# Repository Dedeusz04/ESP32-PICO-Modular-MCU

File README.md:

# ESP32-PICO Modular MCU

A modular hardware design based on the ESP32-PICO microcontroller, split into separate, specialized boards for the processor, power supply, and clock management to ensure high flexibility and easier troubleshooting in embedded development.

## Key Features
- **Modular Architecture**: Core system functionality is divided into distinct, easily interchangeable boards.
- **Processor Module** (`modul_procesora`): Houses the ESP32-PICO core, providing native Wi-Fi/Bluetooth capabilities and GPIO breakouts.
- **Power Supply Module** (`modul_zasilania`): Dedicated hardware for voltage regulation and stable power distribution to all components.
- **Clock Module** (`modul_zegara`): Handles precise clock generation and timing logic.
- **Custom Component Library**: Includes a comprehensive custom Autodesk EAGLE library (`proj_biblioteka.lbr`) with all necessary footprints and symbols used.

For a detailed description of the design, schematic choices, and PCB layouts, refer to the final project report included in this repository: [raport_koncowy_tem1 2 (1).pdf](raport_koncowy_tem1%202%20%281%29.pdf).

## Modules Overview
| Module | Schematic File | Board File | Description |
|---|---|---|---|
| **Processor Module** | `modul_procesora.sch` | `modul_procesora.brd` | Core ESP32-PICO system |
| **Power Supply** | `modul_zasilania.sch` | `modul_zasilania.brd` | Voltage regulation and power management |
| **Clock Module** | `modul_zegara.sch` | `modul_zegara.brd` | Precise timers and RTC |

## Usage
The hardware designs are provided as Autodesk EAGLE files.
1. Clone or download this repository.
2. Open Autodesk EAGLE and ensure `proj_biblioteka.lbr` is added to your active libraries.
3. Open the `.sch` and `.brd` files to view, modify, or manufacture the schematics and PCB designs.

## Contributors
- **Bartosz Kępa**
- **Jan Jamro**
- **Aleksandra Kuś**

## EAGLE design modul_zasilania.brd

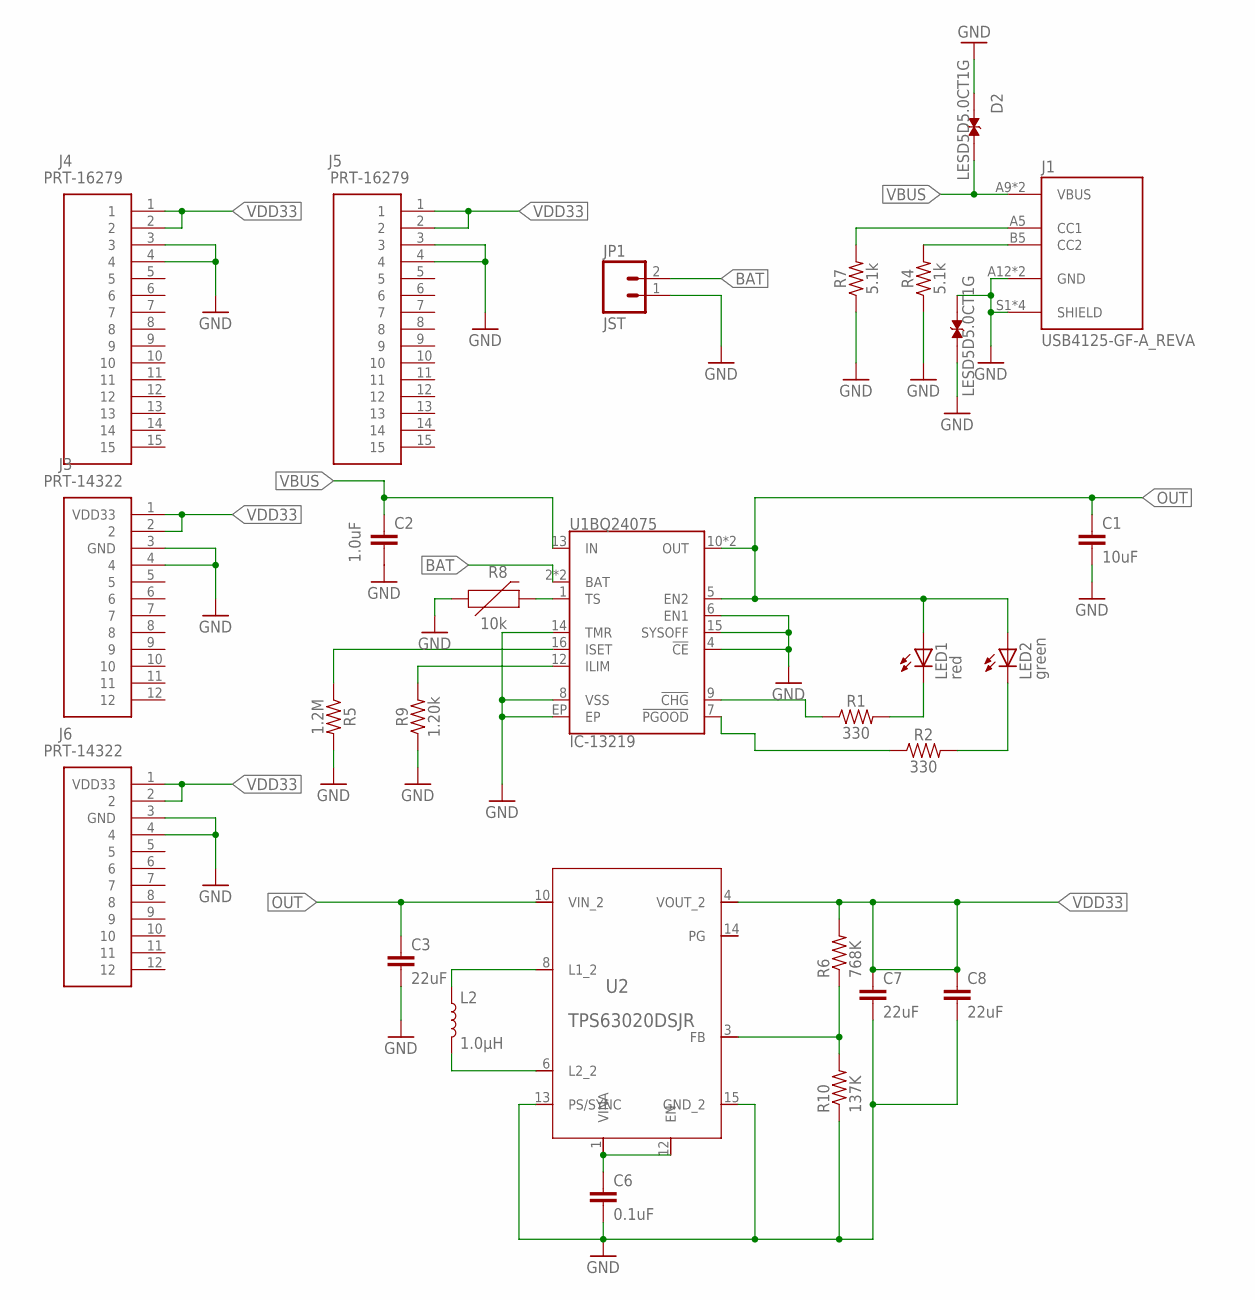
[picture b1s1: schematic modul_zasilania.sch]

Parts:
C1: 10uF; 1206
C2: 1.0uF; 0603
C3, C7, C8: 22uF; 0603
C6: 0.1uF; 0402
D1, D2: LESD5D5.0CT1G; TVS_LESD5D5.0CT1G
J1: USB4125-GF-A_REVA; GCT_USB4125-GF-A_REVA
J3, J6: PRT-14322; RHDR12W87P0X254_1X12_3103X250X
J4, J5: PRT-16279; PRT16279
JP1: JST; JST-2-SMD
L2: 1.0μH; 0805-WIDE
LED1: red; CHIP-LED0805
LED2: green; CHIP-LED0805
R1, R2: 330; 0603
R4, R7: 5.1k; 0603
R5: 1.2M; 0603
R6: 768K; 0603
R8: 10k; 0603@1
R9: 1.20k; 0603
R10: 137K; 0603
U1BQ24075: IC-13219; PVQFN-N16
U2: TPS63020DSJR; R-PVSON-N14

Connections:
BAT: JP1.2, U1BQ24075.2 (BAT), U1BQ24075.3 (BAT)
GND: C1.2, C2.2, C3.2, C6.2, C7.2, C8.2, D1.1, D1.2, D2.1, J1.A12 (GND), J1.B12 (GND), J1.S1 (SHIELD), J1.S2 (SHIELD), J1.S3 (SHIELD), J1.S4 (SHIELD), J3.3 (GND), J3.4, J4.3, J4.4, J5.3, J5.4, J6.3 (GND), J6.4, JP1.1, R4.1, R5.2, R7.1, R8.1, R9.1, R10.1, U1BQ24075.4 (!CE!), U1BQ24075.6 (EN1), U1BQ24075.8 (VSS), U1BQ24075.14 (TMR), U1BQ24075.15 (SYSOFF), U1BQ24075.EP, U2.13 (PS/SYNC), U2.15 (GND_2)
LED1: LED1.C, R1.2
LED2: LED2.C, R2.2
unnamed: R8.2, U1BQ24075.1 (TS)
unnamed: R5.1, U1BQ24075.16 (ISET)
unnamed: J1.B5 (CC2), R4.2
unnamed: J1.A5 (CC1), R7.2
unnamed: R1.1, U1BQ24075.9 (!CHG!)
unnamed: R2.1, U1BQ24075.7 (!PGOOD!)
unnamed: R9.2, U1BQ24075.12 (ILIM)
unnamed: L2.2, U2.6 (L2_2)
unnamed: C6.1, U2.1 (VINA), U2.12 (EN)
unnamed: R6.1, R10.2, U2.3 (FB)
unnamed: L2.1, U2.8 (L1_2)
OUT: C1.1, C3.1, LED1.A, LED2.A, U1BQ24075.5 (EN2), U1BQ24075.10 (OUT), U1BQ24075.11 (OUT), U2.10 (VIN_2)
VBUS: C2.1, D2.2, J1.A9 (VBUS), J1.B9 (VBUS), U1BQ24075.13 (IN)
VDD33: C7.1, C8.1, J3.1 (VDD33), J3.2, J4.1, J4.2, J5.1, J5.2, J6.1 (VDD33), J6.2, R6.2, U2.4 (VOUT_2)

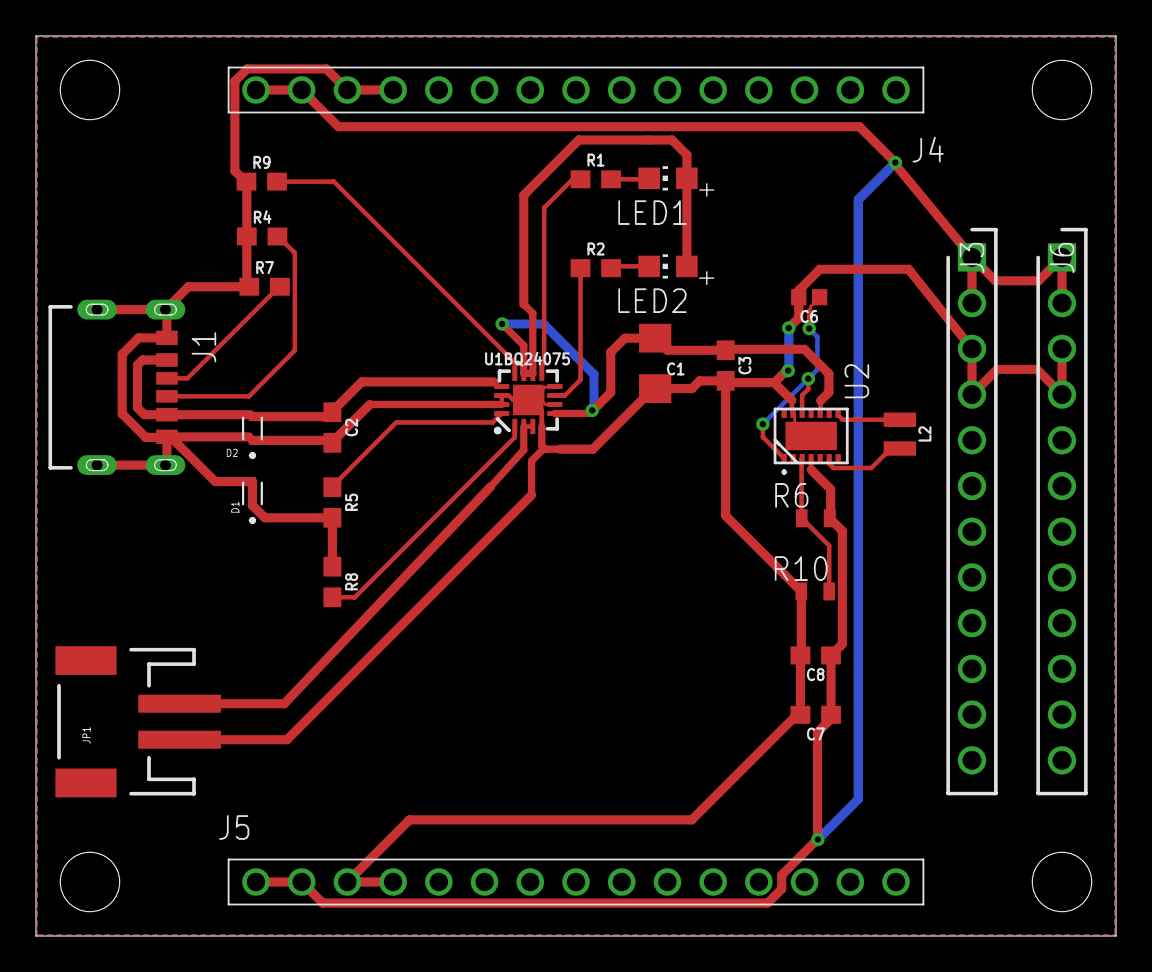
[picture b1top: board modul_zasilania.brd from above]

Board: 2 copper layers, 60.0 x 50.0 mm, 32 parts (0 on the bottom side), 18 nets.

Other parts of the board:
STANDOFF1, STANDOFF2, STANDOFF3, STANDOFF4: STAND-OFF

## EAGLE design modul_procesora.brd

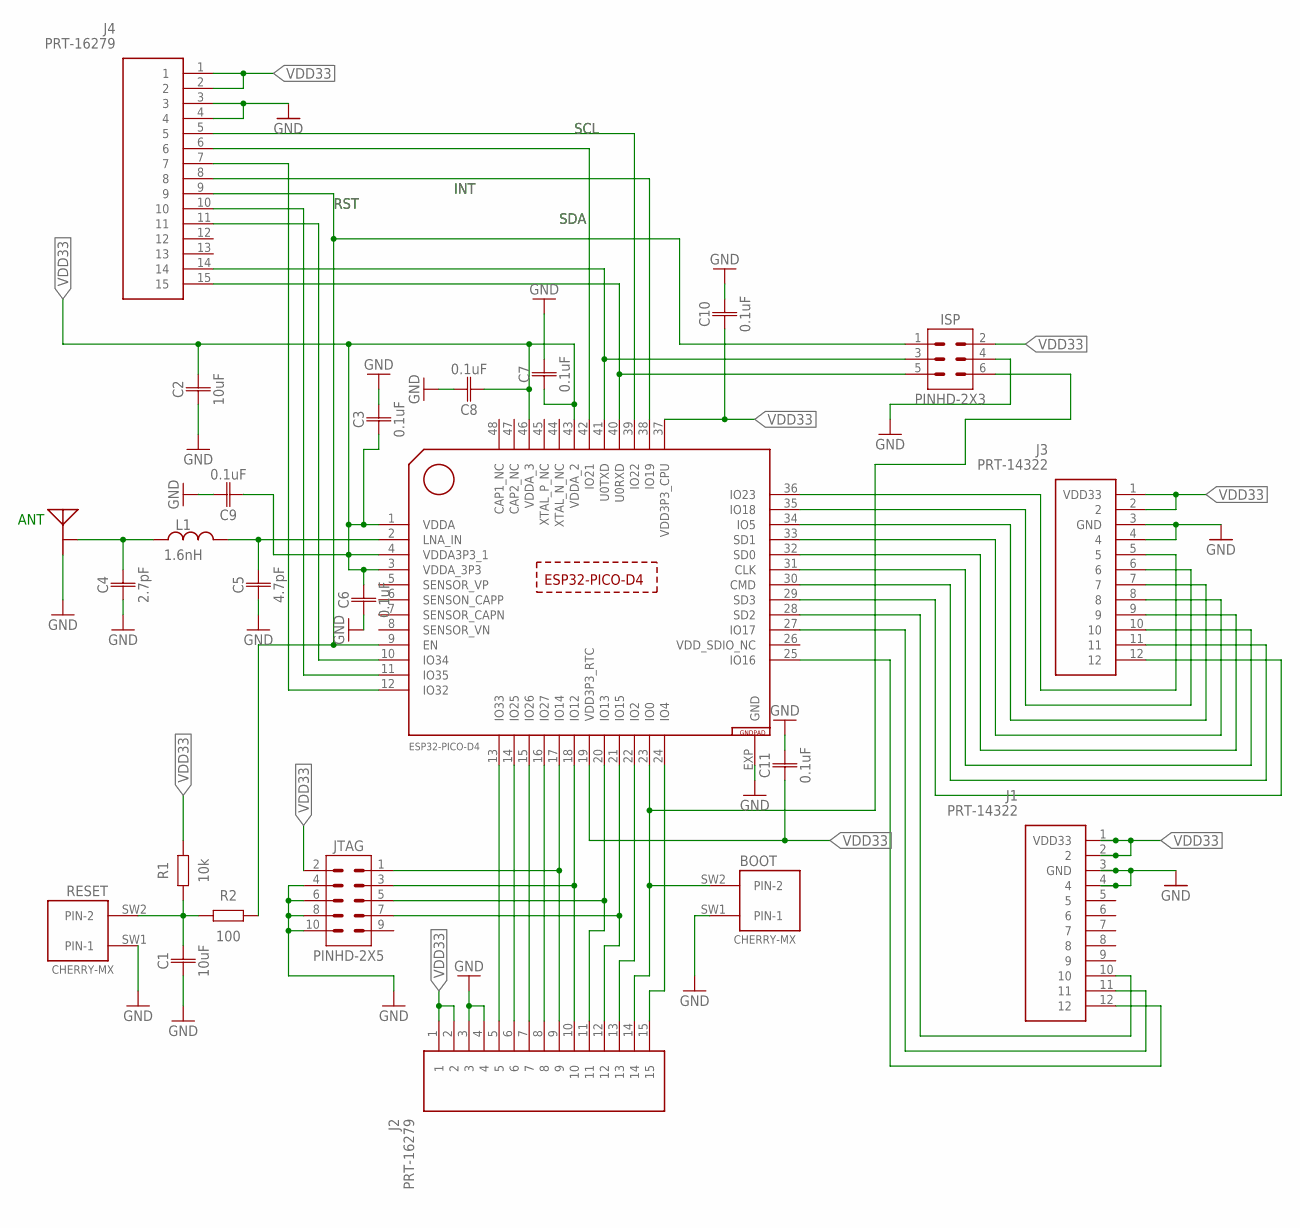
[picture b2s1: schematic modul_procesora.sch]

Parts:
ANT: ANT; MEANDER-ANT
BOOT: BOOT; CHERRY-MX
C1, C2: 10uF; CAPC1005X60
C3, C6, C7, C8, C9, C10, C11: 0.1uF; CAPC1005X60
C4: 2.7pF; CAPC1005X60
C5: 4.7pF; CAPC1005X60
ISP: PINHD-2X3; 2X03
J1, J3: PRT-14322; RHDR12W87P0X254_1X12_3103X250X
J2, J4: PRT-16279; PRT16279
JTAG: PINHD-2X5; 2X05
L1: 1.6nH; INDC1006X60N
R1: 10k; RESC1005X40
R2: 100; RESC1005X40
RESET: CHERRY-MX
U$1: ESP32-PICO-D4; QFN48

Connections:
GND: ANT.FEED, BOOT.SW1 (PIN-1), C1.1, C2.1, C3.2, C4.1, C5.1, C6.1, C7.2, C8.2, C9.2, C10.2, C11.2, ISP.4, J1.3 (GND), J1.4, J2.3, J2.4, J3.3 (GND), J3.4, J4.3, J4.4, JTAG.4, JTAG.6, JTAG.8, JTAG.10, RESET.SW1 (PIN-1), U$1.EXP (GND)
INT: J4.8, U$1.38 (IO19)
unnamed: BOOT.SW2 (PIN-2), ISP.6, J2.14, U$1.23 (IO0)
unnamed: C1.2, R1.1, R2.1, RESET.SW2 (PIN-2)
unnamed: J2.9, JTAG.1, U$1.17 (IO14)
unnamed: J2.10, JTAG.3, U$1.18 (IO12)
unnamed: J2.11, JTAG.5, U$1.20 (IO13)
unnamed: J2.12, JTAG.7, U$1.21 (IO15)
unnamed: ISP.5, J4.15, U$1.40 (U0RXD)
unnamed: ISP.3, J4.14, U$1.41 (U0TXD)
unnamed: ANT.GND, C4.2, L1.1
unnamed: C5.2, L1.2, U$1.2 (LNA_IN)
unnamed: J3.5, U$1.36 (IO23)
unnamed: J3.6, U$1.35 (IO18)
unnamed: J3.7, U$1.34 (IO5)
unnamed: J3.8, U$1.33 (SD1)
unnamed: J3.9, U$1.32 (SD0)
unnamed: J3.10, U$1.31 (CLK)
unnamed: J3.11, U$1.30 (CMD)
unnamed: J3.12, U$1.29 (SD3)
unnamed: J1.10, U$1.28 (SD2)
unnamed: J1.11, U$1.27 (IO17)
unnamed: J1.12, U$1.25 (IO16)
unnamed: J2.15, U$1.24 (IO4)
unnamed: J2.13, U$1.22 (IO2)
unnamed: J2.8, U$1.16 (IO27)
unnamed: J2.7, U$1.15 (IO26)
unnamed: J2.6, U$1.14 (IO25)
unnamed: J2.5, U$1.13 (IO33)
unnamed: J4.7, U$1.12 (IO32)
unnamed: J4.10, U$1.11 (IO35)
unnamed: J4.11, U$1.10 (IO34)
RST: ISP.1, J4.9, R2.2, U$1.9 (EN)
SCL: J4.5, U$1.39 (IO22)
SDA: J4.6, U$1.42 (IO21)
VDD33: C2.2, C3.1, C6.2, C7.1, C8.1, C9.1, C10.1, C11.1, ISP.2, J1.1 (VDD33), J1.2, J2.1, J2.2, J3.1 (VDD33), J3.2, J4.1, J4.2, JTAG.2, R1.2, U$1.1 (VDDA), U$1.3 (VDDA_3P3), U$1.4 (VDDA3P3_1), U$1.19 (VDD3P3_RTC), U$1.37 (VDD3P3_CPU), U$1.43 (VDDA_2), U$1.46 (VDDA_3)
VDD_SDIO_NC: U$1.26 (VDD_SDIO_NC)

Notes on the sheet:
ANT
SDA
INT
RST
SCL

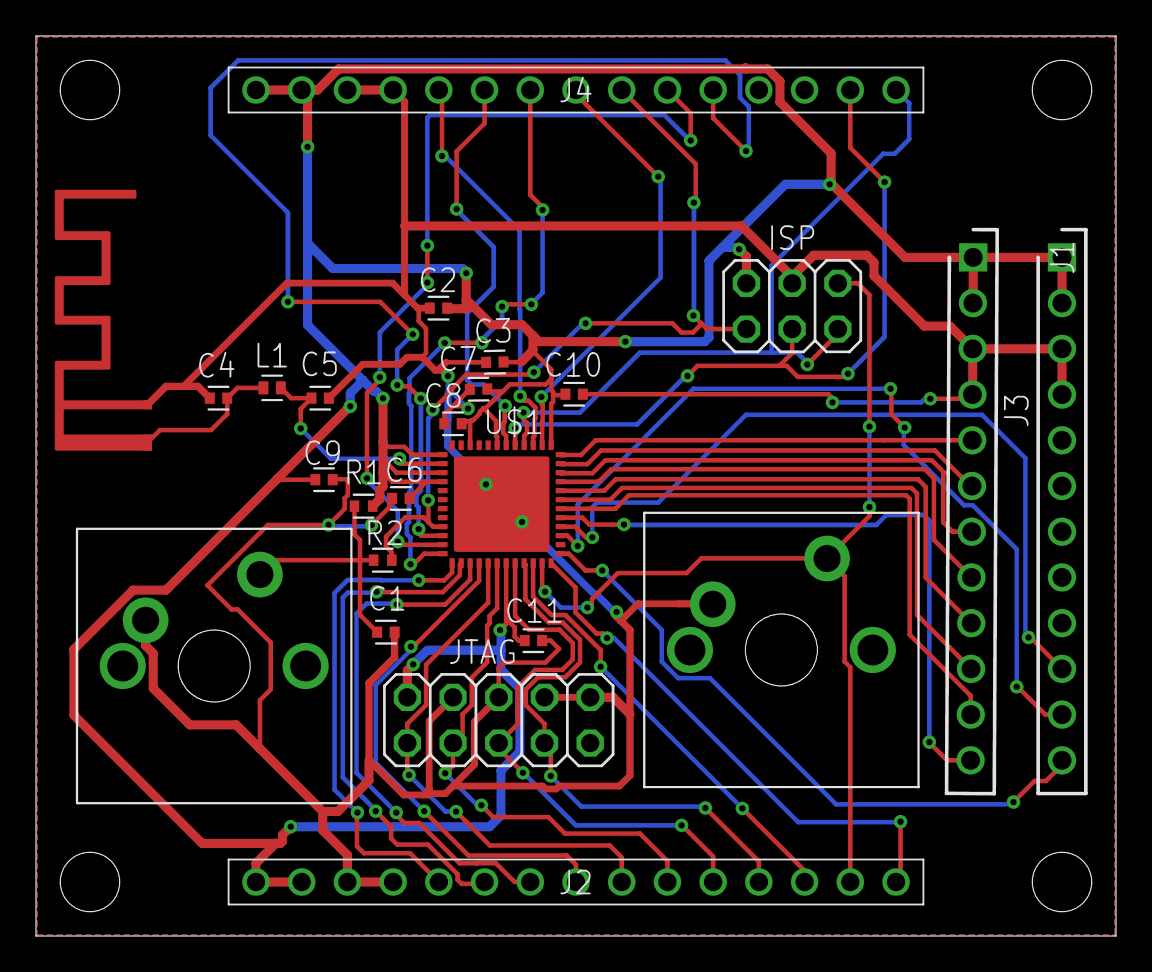
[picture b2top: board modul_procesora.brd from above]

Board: 2 copper layers, 60.0 x 50.0 mm, 28 parts (0 on the bottom side), 36 nets.

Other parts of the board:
STANDOFF1, STANDOFF2, STANDOFF3, STANDOFF4: STAND-OFF

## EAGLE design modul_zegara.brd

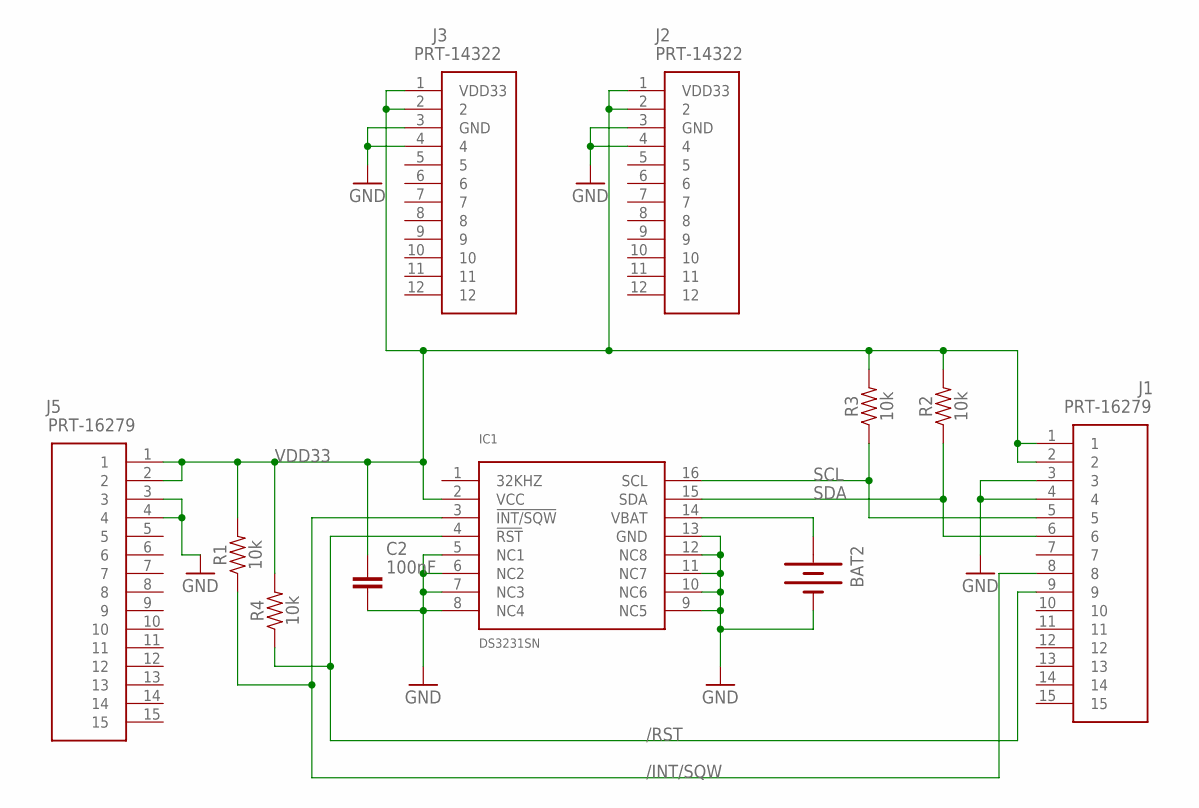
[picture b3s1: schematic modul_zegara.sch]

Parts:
BAT2: BATTERY20PTH; BATTCOM_20MM_PTH
C2: 100nF; CAPC3216X135
IC1: DS3231SN; SO16W
J1, J5: PRT-16279; PRT16279
J2, J3: PRT-14322; RHDR12W87P0X254_1X12_3103X250X
R1, R2, R3, R4: 10k; AXIAL-0.3

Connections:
/INT/SQW: IC1.3 (!INT/SQW), J1.8, R1.P$1 (1)
/RST: IC1.4 (!RST), J1.9, R4.P$1 (1)
GND: BAT2.2 (-), C2.2, IC1.5 (NC1), IC1.6 (NC2), IC1.7 (NC3), IC1.8 (NC4), IC1.9 (NC5), IC1.10 (NC6), IC1.11 (NC7), IC1.12 (NC8), IC1.13 (GND), J1.3, J1.4, J2.3 (GND), J2.4, J3.3 (GND), J3.4, J5.3, J5.4
unnamed: BAT2.1 (+), IC1.14 (VBAT)
SCL: IC1.16 (SCL), J1.5, R3.P$1 (1)
SDA: IC1.15 (SDA), J1.6, R2.P$1 (1)
VDD33: C2.1, IC1.2 (VCC), J1.1, J1.2, J2.1 (VDD33), J2.2, J3.1 (VDD33), J3.2, J5.1, J5.2, R1.P$2 (2), R2.P$2 (2), R3.P$2 (2), R4.P$2 (2)

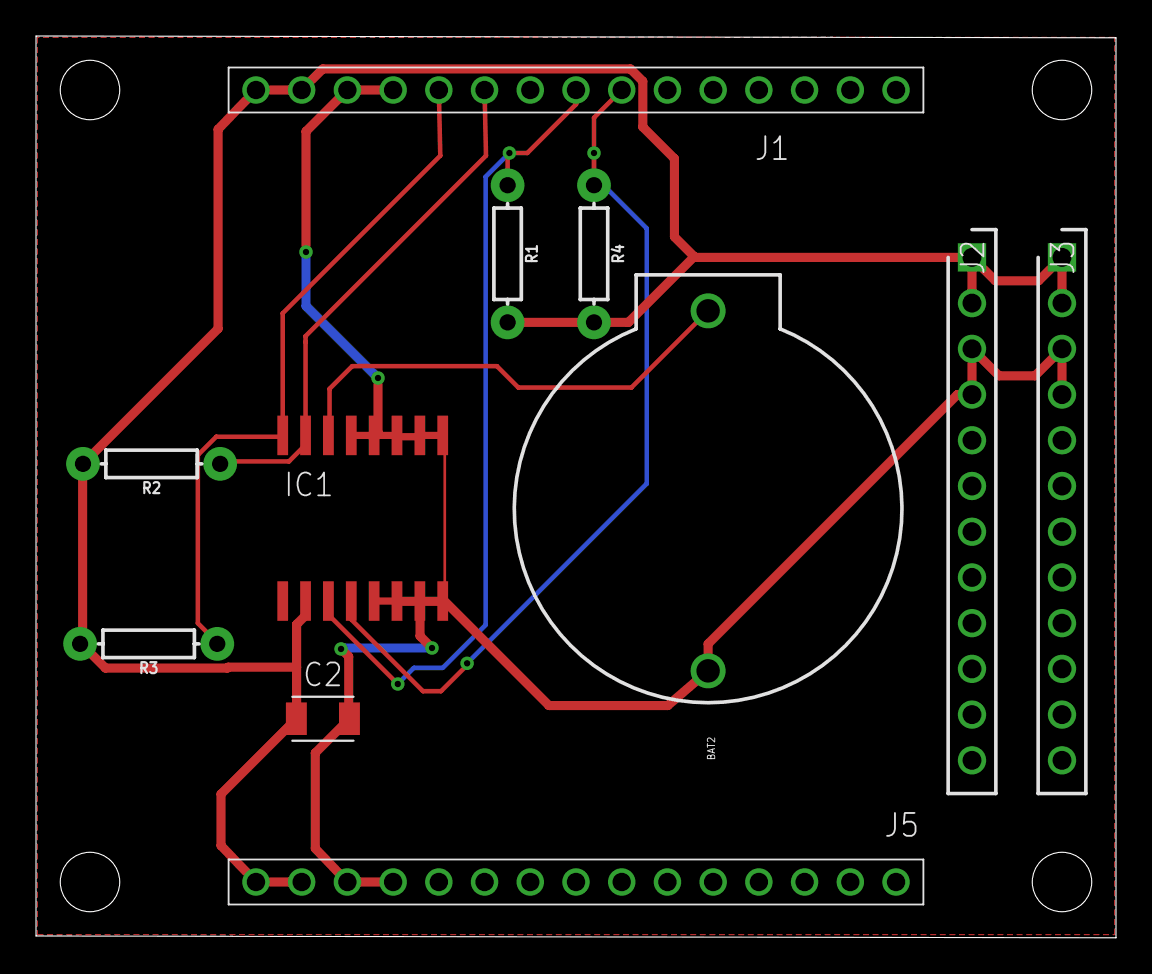
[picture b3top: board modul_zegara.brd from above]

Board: 2 copper layers, 60.0 x 50.1 mm, 15 parts (0 on the bottom side), 7 nets.

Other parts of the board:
STANDOFF1, STANDOFF2, STANDOFF3, STANDOFF4: STAND-OFF

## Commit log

2026-03-22 Initial commit with EAGLE files and README
2026-03-22 Add contributors Bartosz Kępa, Jan Jamro, Aleksandra Kuś

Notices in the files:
parts and their libraries:
SparkFun-Electromechanical: Licensing: Creative Commons ShareAlike 4.0 International - https://creativecommons.org/licenses/by-sa/4.0
SparkFun: Licensing: CC v3.0 Share-Alike You are welcome to use this library for commercial purposes.
